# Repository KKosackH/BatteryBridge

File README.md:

# BatteryBridge  

The **BatteryBridge** is a PowerPath control circuit that ensures the essential electronics on the SwitchSystem PCB remain powered during grid disconnection.  

The SwitchSystem PCB only receives power when the home charger is in **IEC 61851 Control Pilot state C** (charging mode). When transitioning from charging to discharging, the PCB would normally lose power. The BatteryBridge solves this by automatically switching to battery supply, keeping the system running seamlessly.  

---

## Features  
- **Power continuity**: Maintains operation when the grid is disconnected or charger state changes.  
- **Integrated converters**: High-efficiency buck and boost converters for multiple voltage rails.  
- **PowerPath control**: Manages seamless switching between charger and battery.  
- **Battery charging**: Supports onboard Li-ion battery charging.  
- **Multiple outputs**: 3.3 V, 5 V, and 12 V regulated outputs (v1 only included 3.3 V and 5 V).  

---

## Design  
The BatteryBridge PCB consists of three main parts:  
1. High-efficiency buck and boost converters  
2. PowerPath controller  
3. Battery charger  

For the prototype, a **3.7V battery** was used. Long-life battery options are being evaluated with manufacturers to ensure durability of the add-on solution.  

The schematic is organized hierarchically, with the root showing all user-interactable components.  

---

## Operation  
- **State C (charging)**:  
  - The battery charges.  
  - Outputs are disabled (system powered directly from charger).  

- **Other states (discharging / grid disconnected)**:  
  - Outputs are enabled.  
  - Battery supplies regulated 3.3 V, 5 V, and 12 V rails to the SwitchSystem PCB via two JST connectors.  

---

## PCB Images  

### Front Side  

### Back Side  

---

## Outputs  
- **3.3 V**  
- **5 V**  
- **12 V**  

These outputs are used primarily to power the Raspberry Pi and essential circuits on the SwitchSystem PCB.

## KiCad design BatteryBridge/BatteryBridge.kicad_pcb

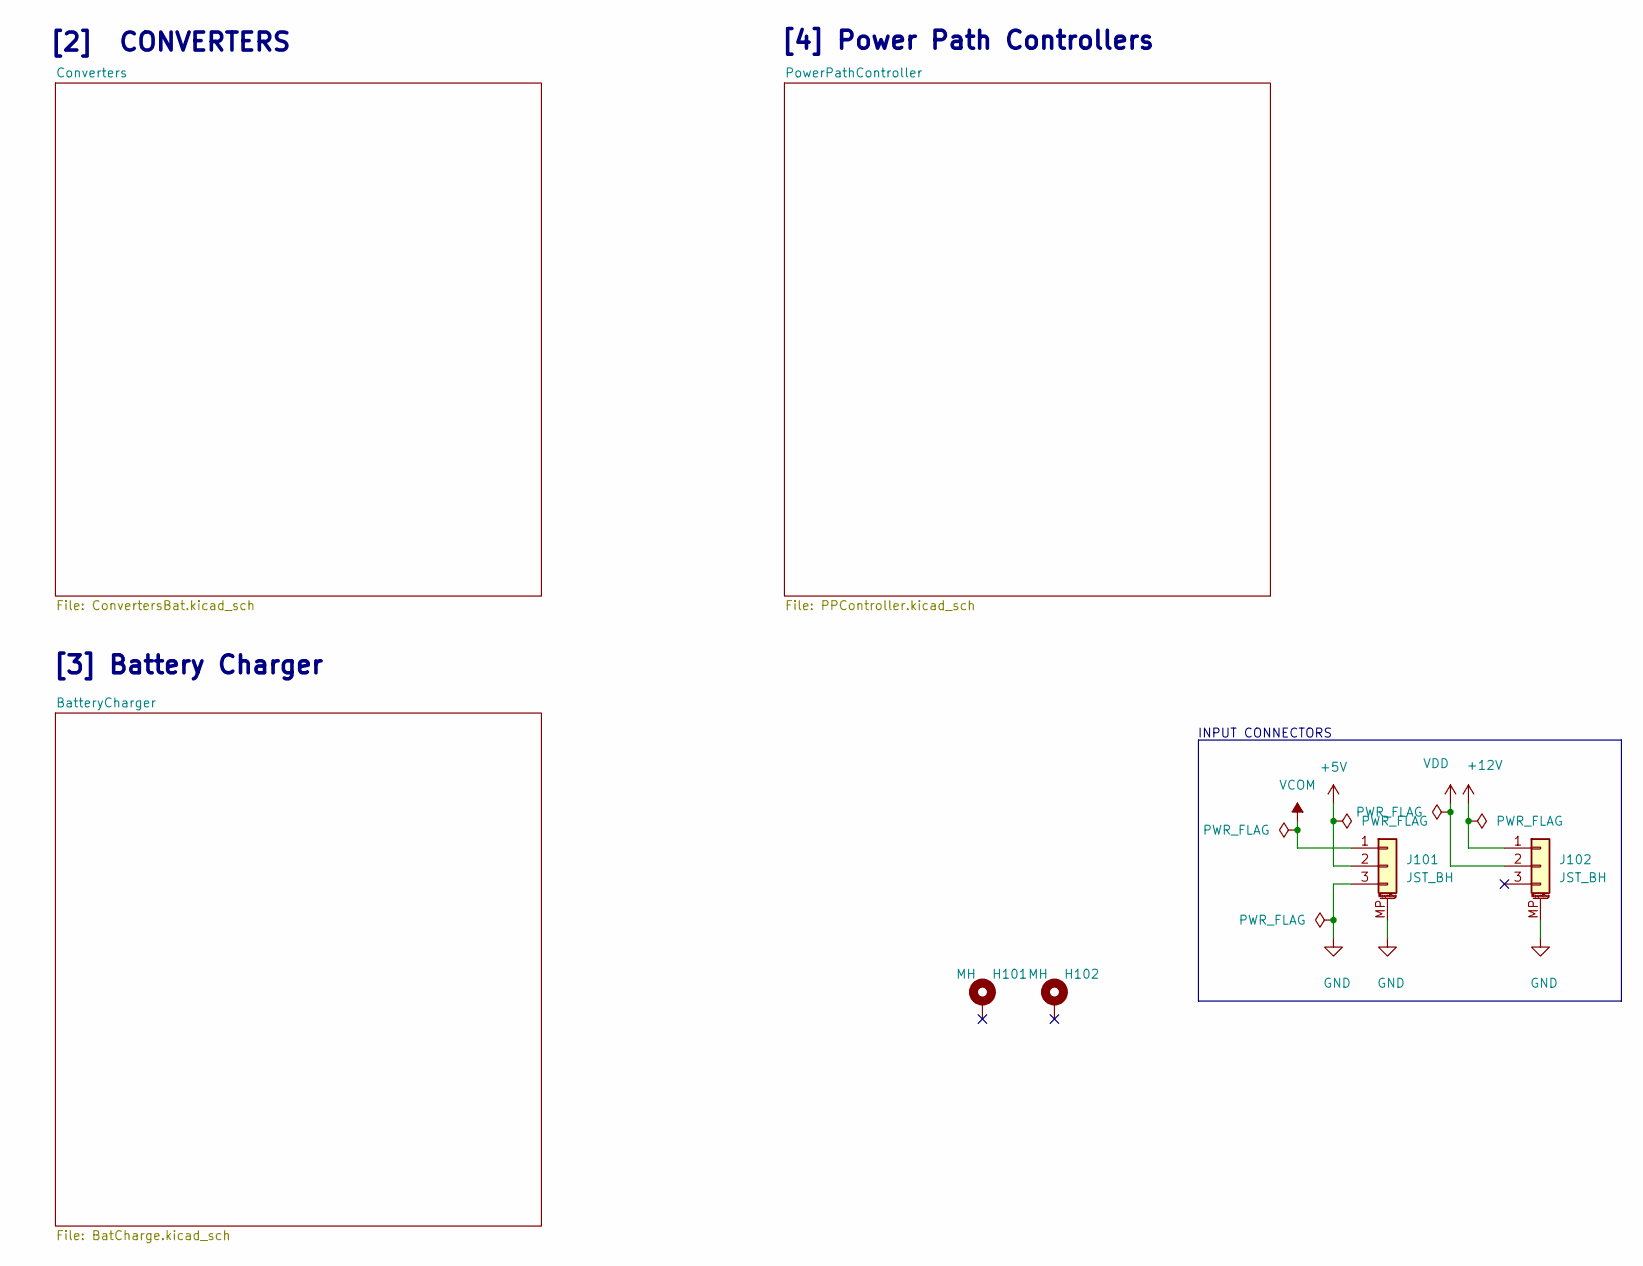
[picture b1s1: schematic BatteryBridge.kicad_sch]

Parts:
H101: MH; MountingHole_3.2mm_M3_Pad_Via
H102: MH; MountingHole_2.2mm_M2_Pad_TopOnly
J101, J102: JST_BH; JST_GH_SM03B-GHS-TB_1x03-1MP_P1.25mm_Horizontal

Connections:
+5V: J101.2; also elsewhere on the board
+12V: J102.1; also elsewhere on the board
GND: J101.3, J101.MP (MountPin), J102.MP (MountPin); also elsewhere on the board
VCOM: J101.1; also elsewhere on the board
VDD: J102.2; also elsewhere on the board

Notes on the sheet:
INPUT CONNECTORS
[2] CONVERTERS
[3] Battery Charger
[4] Power Path Controllers

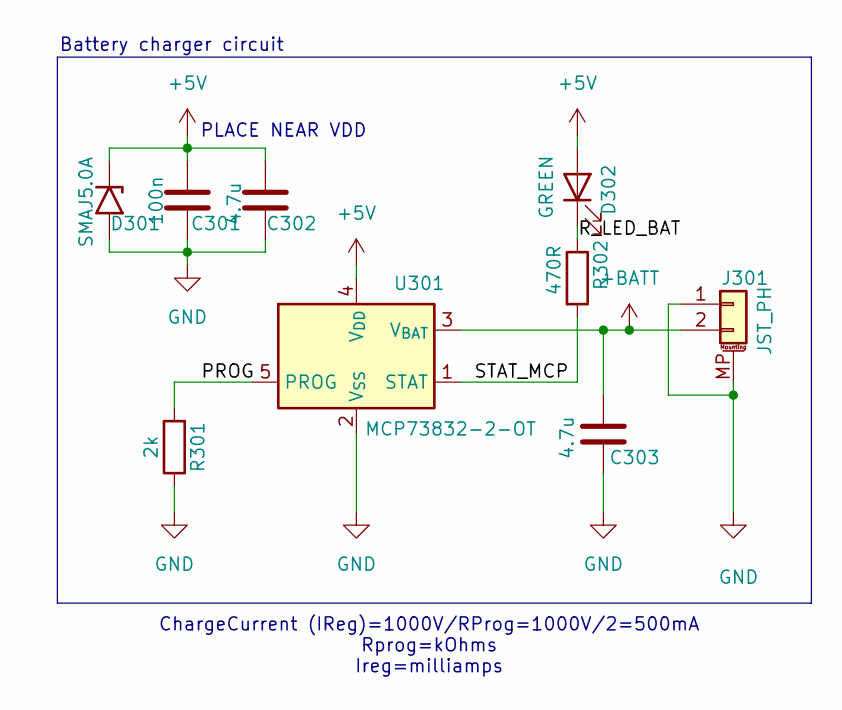
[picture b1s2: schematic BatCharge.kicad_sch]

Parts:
C301: 100n; C_0805_2012Metric
C302, C303: 4.7u; C_0805_2012Metric
D301: SMAJ5.0A; D_SMA
D302: GREEN; LED_0805_2012Metric
J301: JST_PH; JST_PH_S2B-PH-SM4-TB_1x02-1MP_P2.00mm_Horizontal
R301: 2k; R_0805_2012Metric
R302: 470R; R_0805_2012Metric
U301: MCP73832-2-OT; SOT-23-5

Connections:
+5V: C301.2, C302.2, D301.1 (A1), D302.2 (A), U301.4 (V_{DD}); also elsewhere on the board
+BATT: C303.2, J301.2, U301.3 (V_{BAT}); also elsewhere on the board
/BatteryCharger/PROG: R301.2, U301.5 (PROG)
/BatteryCharger/R_LED_BAT: D302.1 (K), R302.1
/BatteryCharger/STAT_MCP: R302.2, U301.1 (STAT)
GND: C301.1, C302.1, C303.1, D301.2 (A2), J301.1, J301.MP (MountPin), R301.1, U301.2 (V_{SS}); also elsewhere on the board

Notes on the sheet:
Battery charger circuit
PLACE NEAR VDD
ChargeCurrent (IReg)=1000V/RProg=1000V/2=500mA Rprog=kOhms Ireg=milliamps

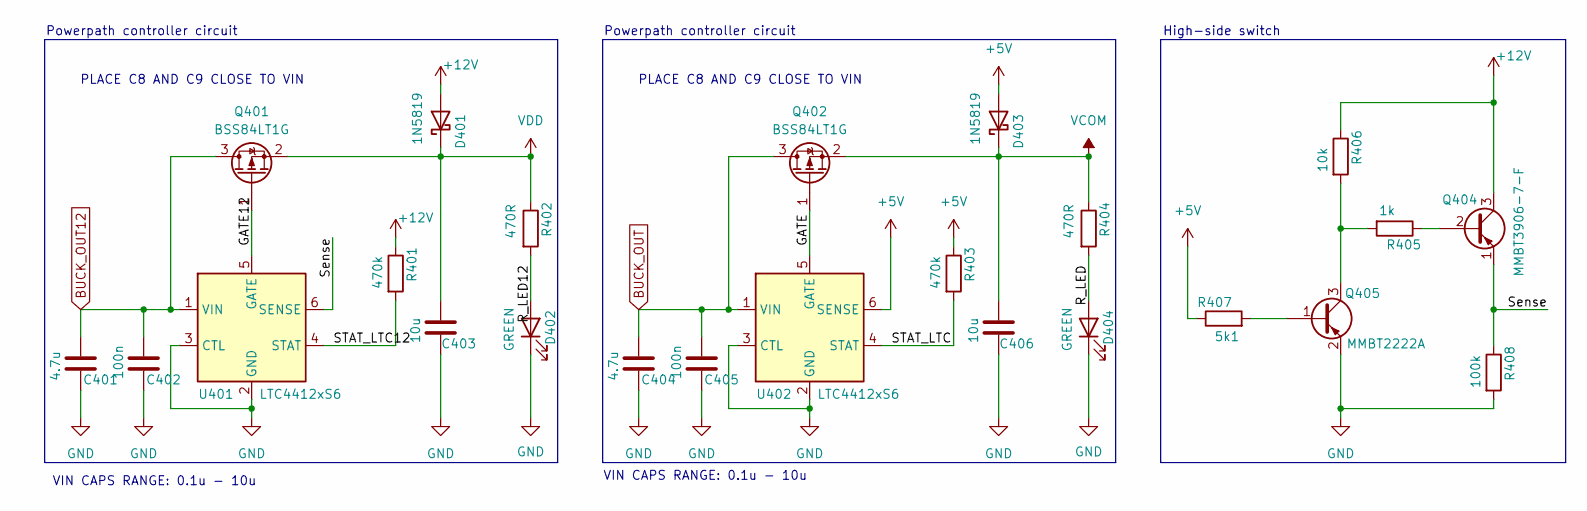
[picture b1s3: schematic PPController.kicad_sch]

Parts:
C401, C404: 4.7u; C_0805_2012Metric
C402, C405: 100n; C_0805_2012Metric
C403, C406: 10u; C_0805_2012Metric
D401, D403: 1N5819; D_DO-41_SOD81_P7.62mm_Horizontal
D402, D404: GREEN; LED_0805_2012Metric
Q401, Q402: BSS84LT1G; SOT-23
Q404: MMBT3906-7-F; SOT-23-3
Q405: MMBT2222A; SOT-23-3
R401, R403: 470k; R_0805_2012Metric
R402, R404: 470R; R_0805_2012Metric
R405: 1k; R_0805_2012Metric
R406: 10k; R_0805_2012Metric
R407: 5k1; R_0805_2012Metric
R408: 100k; R_0805_2012Metric
U401, U402: LTC4412xS6; TSOT-23-6

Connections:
+5V: D403.2 (A), R403.1, R407.1, U402.6 (SENSE); also elsewhere on the board
+12V: D401.2 (A), Q404.3 (C), R401.1, R406.1; also elsewhere on the board
/PowerPathController/GATE: Q402.1 (G), U402.5 (GATE)
/PowerPathController/GATE12: Q401.1 (G), U401.5 (GATE)
/PowerPathController/R_LED: D404.2 (A), R404.2
/PowerPathController/R_LED12: D402.2 (A), R402.2
/PowerPathController/STAT_LTC: R403.2, U402.4 (STAT)
/PowerPathController/STAT_LTC12: R401.2, U401.4 (STAT)
/PowerPathController/Sense: Q404.1 (E), R408.1, U401.6 (SENSE)
BUCK_OUT: C404.2, C405.2, Q402.3 (D), U402.1 (VIN); also elsewhere on the board
BUCK_OUT12: C401.2, C402.2, Q401.3 (D), U401.1 (VIN); also elsewhere on the board
GND: C401.1, C402.1, C403.2, C404.1, C405.1, C406.2, D402.1 (K), D404.1 (K), Q405.2 (E), R408.2, U401.2 (GND), U401.3 (CTL), U402.2 (GND), U402.3 (CTL); also elsewhere on the board
unnamed: Q404.2 (B), R405.1
unnamed: Q405.1 (B), R407.2
unnamed: Q405.3 (C), R405.2, R406.2
VCOM: C406.1, D403.1 (K), Q402.2 (S), R404.1; also elsewhere on the board
VDD: C403.1, D401.1 (K), Q401.2 (S), R402.1; also elsewhere on the board

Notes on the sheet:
Powerpath controller circuit
PLACE C8 AND C9 CLOSE TO VIN
High-side switch
VIN CAPS RANGE: 0.1u - 10u

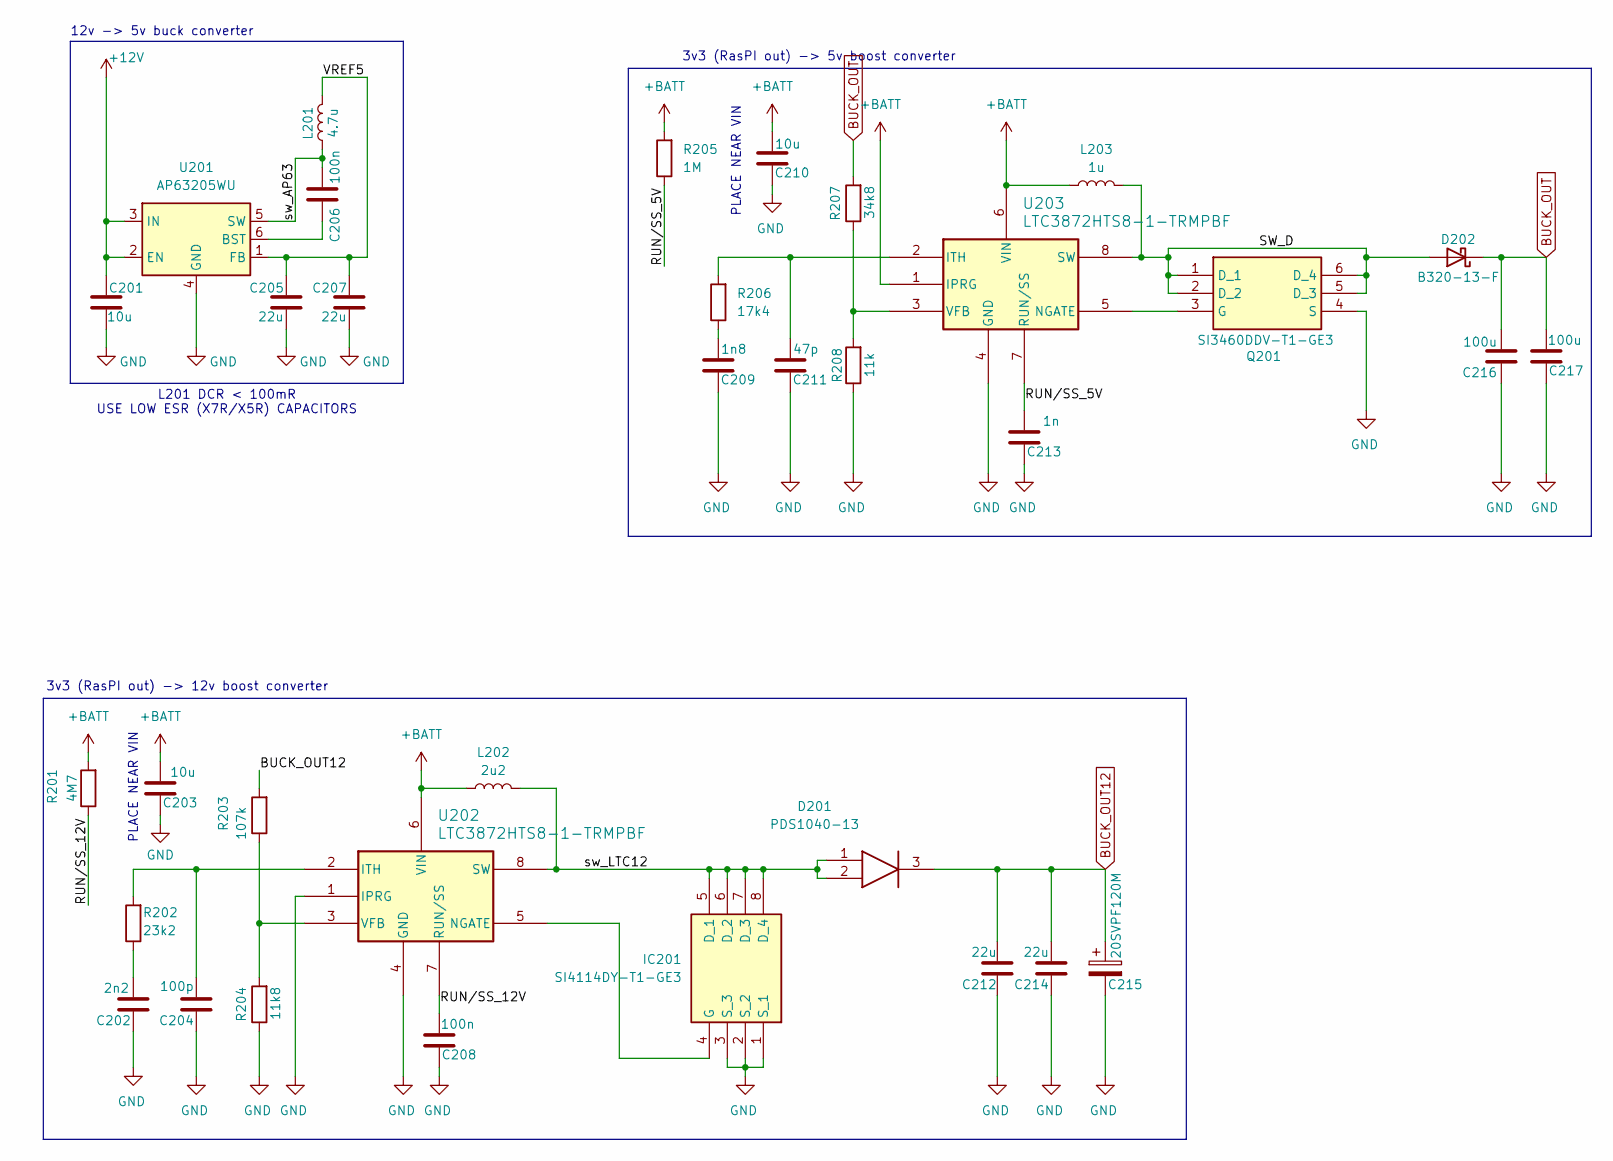
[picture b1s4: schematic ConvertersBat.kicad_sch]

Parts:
C201, C203, C210: 10u; C_0805_2012Metric
C202: 2n2; C_0805_2012Metric
C204: 100p; C_0805_2012Metric
C205, C207: 22u; C_0805_2012Metric
C206, C208: 100n; C_0805_2012Metric
C209: 1n8; C_0805_2012Metric
C211: 47p; C_0805_2012Metric
C212, C214: 22u; C_1210_3225Metric
C213: 1n; C_0805_2012Metric
C215: 20SVPF120M; 16SVF180M
C216, C217: 100u; C_0805_2012Metric
D201: PDS1040-13; PDS104013; Mouser Part Number 621-PDS1040-13
D202: B320-13-F; D_SMC
IC201: SI4114DY-T1-GE3; SOIC127P600X175-8N; Mouser Part Number 781-SI4114DY-T1-GE3
L201: 4.7u; HCM1A0805-4R7-R
L202: 2u2; DR125-2R2-R
L203: 1u; PA4341.102NLT
Q201: SI3460DDV-T1-GE3; TSOP-6_1.65x3.05mm_P0.95mm; Mouser Part Number 781-SI3460DDV-T1-GE3
R201: 4M7; R_0805_2012Metric
R202: 23k2; R_0805_2012Metric
R203: 107k; R_0805_2012Metric
R204: 11k8; R_0805_2012Metric
R205: 1M; R_0805_2012Metric
R206: 17k4; R_0805_2012Metric
R207: 34k8; R_0805_2012Metric
R208: 11k; R_0805_2012Metric
U201: AP63205WU; TSOT-23-6
U202, U203: LTC3872HTS8-1-TRMPBF; TSOT-23-8_HandSoldering

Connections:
+12V: C201.2, U201.2 (EN), U201.3 (IN); also elsewhere on the board
+BATT: C203.1, C210.1, L202.1, L203.1, R201.2, R205.2, U202.6 (VIN), U203.1 (IPRG), U203.6 (VIN); also elsewhere on the board
/Converters/RUN/SS_5V: C213.1, R205.1, U203.7 (RUN/SS)
/Converters/RUN/SS_12V: C208.1, R201.1, U202.7 (RUN/SS)
/Converters/SW_D: D202.2 (A), L203.2, Q201.1 (D_1), Q201.2 (D_2), Q201.5 (D_3), Q201.6 (D_4), U203.8 (SW)
/Converters/VREF5: C205.2, C207.2, L201.2, U201.1 (FB)
/Converters/sw_AP63: C206.1, L201.1, U201.5 (SW)
/Converters/sw_LTC12: D201.1 (A1), D201.2 (A2), IC201.5 (D_1), IC201.6 (D_2), IC201.7 (D_3), IC201.8 (D_4), L202.2, U202.8 (SW)
BUCK_OUT: C216.1, C217.1, D202.1 (K), R207.2; also elsewhere on the board
BUCK_OUT12: C212.1, C214.1, C215.1, D201.3 (K), R203.2; also elsewhere on the board
GND: C201.1, C202.2, C203.2, C204.2, C205.1, C207.1, C208.2, C209.2, C210.2, C211.2, C212.2, C213.2, C214.2, C215.2, C216.2, C217.2, IC201.1 (S_1), IC201.2 (S_2), IC201.3 (S_3), Q201.4 (S), R204.1, R208.1, U201.4 (GND), U202.1 (IPRG), U202.4 (GND), U203.4 (GND); also elsewhere on the board
unnamed: C202.1, R202.1
unnamed: C209.1, R206.1
unnamed: IC201.4 (G), U202.5 (NGATE)
unnamed: Q201.3 (G), U203.5 (NGATE)
unnamed: C206.2, U201.6 (BST)
unnamed: C204.1, R202.2, U202.2 (ITH)
unnamed: R203.1, R204.2, U202.3 (VFB)
unnamed: C211.1, R206.2, U203.2 (ITH)
unnamed: R207.1, R208.2, U203.3 (VFB)

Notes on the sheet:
12v -> 5v buck converter
PLACE NEAR VIN
3v3 (RasPI out) -> 5v boost converter
L201 DCR < 100mR USE LOW ESR (X7R/X5R) CAPACITORS
3v3 (RasPI out) -> 12v boost converter

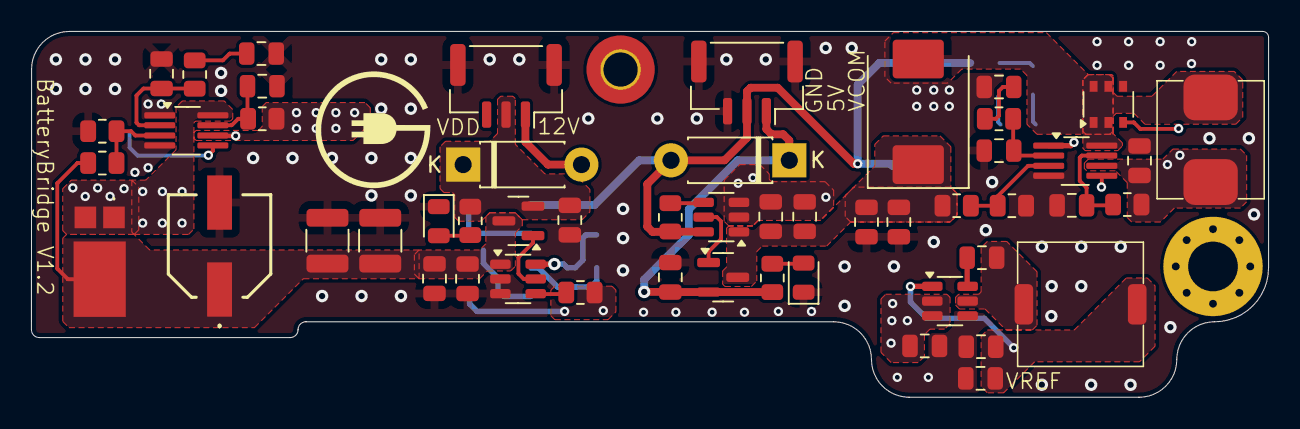
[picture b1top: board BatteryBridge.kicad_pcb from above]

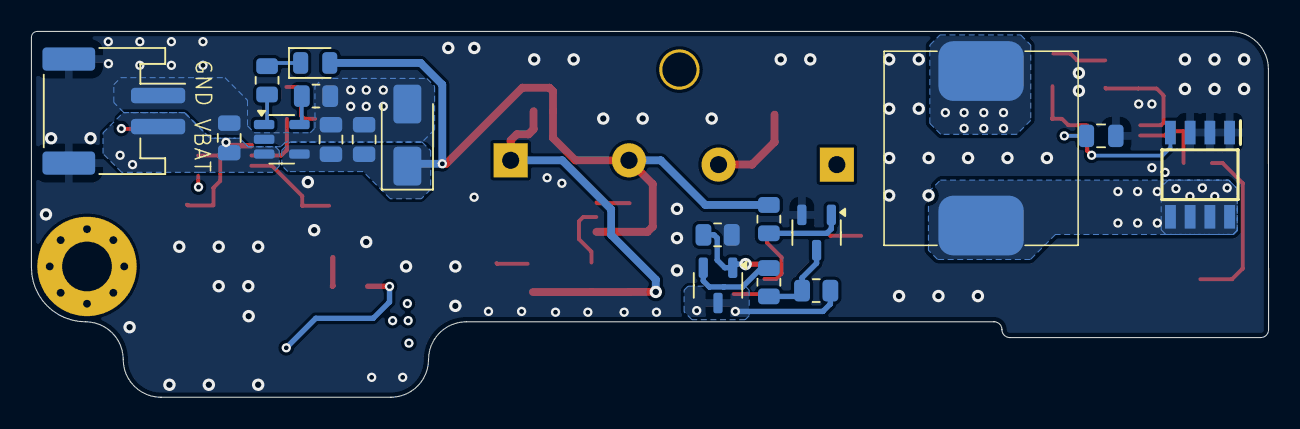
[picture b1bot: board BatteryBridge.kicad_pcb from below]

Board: 6 copper layers, 79.7 x 23.6 mm, 72 parts (18 on the bottom side), 36 nets.

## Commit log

2024-06-27 First commit, finished V1, needs logo
2024-10-16 Finished V1.1, added gerbers/drills
2024-10-16 Init v1.2
2024-10-18 Finished schematic and component selection
2024-10-20 Started layout labtop
2024-10-21 Finished v1.2, added gerbers
2025-09-30 Added pictures and updated readme
2025-09-30 Fixed path
2025-09-30 Fixed picture path
2025-09-30 readme update
2025-09-30 Final version of README
